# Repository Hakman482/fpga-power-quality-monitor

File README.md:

# FPGA-Based Single-Phase Power Quality Monitor

A complete hardware–FPGA–software prototype for real-time single-phase power-quality measurement, developed as an MSc Electronic & Electrical Engineering project.

The system combines a custom 4-layer sensing/conditioning PCB, dual 16-bit SAR ADC acquisition, a Nexys A7-100T FPGA processing pipeline, UART telemetry, and a Python desktop GUI. The implementation measures and visualises RMS voltage/current, frequency, active/apparent power, power factor, harmonic distortion, raw ADC samples, waveforms, and voltage-event conditions.

> **Safety:** the hardware includes circuitry intended to interface with hazardous AC voltages. The prototype is an academic/laboratory design, not a certified measurement instrument. Do not connect it to mains unless you are qualified to work on hazardous voltages and have independently verified isolation, protection, creepage/clearance, grounding, enclosure and test procedures.

## Project highlights

- Custom **4-layer PCB** for isolated voltage sensing and Hall-effect current sensing.
- Two synchronized **ADS8320 16-bit SAR ADC** channels.
- **Nexys A7-100T / Artix-7** FPGA (`xc7a100tcsg324-1`).
- **10 kS/s per channel** synchronized acquisition.
- FPGA implementations for cycle-synchronous RMS, frequency measurement, active/apparent power, power factor, adaptive harmonic analysis through the 25th harmonic, and THD calculation.
- Real-data mode selected in the supplied top-level design (`TEST_MODE => false`).
- **115200-baud UART** with separate metric and waveform/raw-ADC packet formats.
- Python/Tkinter GUI with live dashboard, waveforms, raw ADC view, spectrum, events, validation tools and CSV recording.
- Experimental validation using function-generator voltage tests and DC current calibration, with measurement-uncertainty analysis.

## System architecture

`Voltage / Current sensing -> analogue conditioning -> dual ADC -> FPGA acquisition/DSP -> UART -> Python GUI`

### Measurement hardware

The voltage path uses an isolated-amplifier-based sensing chain followed by precision op-amp conditioning and anti-alias filtering before conversion by an ADS8320.

Current is sensed using an ACS724 Hall-effect sensor, conditioned around the analogue midpoint, filtered and digitised by the second ADS8320.

## FPGA architecture

The final hardware design is in [`fpga/`](fpga/).

| Parameter | Value |
|---|---:|
| FPGA | Nexys A7-100T / `xc7a100tcsg324-1` |
| System clock | 100 MHz |
| ADC serial clock | 500 kHz |
| Sampling rate | 10 kS/s/channel |
| Nominal mains frequency | 50 Hz |
| Nominal RMS/power window | 200 samples |
| Maximum adaptive THD cycle frame | 210 samples |
| UART | 115200 baud, 8N1 |
| Waveform frame | 1000 sample pairs |
| Waveform capture interval | approximately 2 s |

See [`fpga/README.md`](fpga/README.md) for the module breakdown and Vivado build instructions.

## UART protocol and GUI

Two packet families are transmitted:

- `AA55`: FPGA-computed power-quality metrics.
- `AA56`: versioned V/I sample frames containing raw 16-bit ADC codes and scaled engineering-unit samples.

A 1000-pair frame represents 100 ms of data at 10 kS/s, or about five cycles of a 50 Hz waveform. Continuous raw streaming is deliberately avoided because 115200-baud UART cannot carry the full 10 kS/s sample stream continuously.

The Python GUI is in [`gui/`](gui/).

```bash
cd gui
python -m pip install -r requirements.txt
python main.py
```

## Validation

The project was validated using low-voltage sinusoidal input tests for the voltage chain and DC current calibration for the current chain. Oscilloscope/logic measurements were also used to verify conversion cadence, ADC serial-clock bursts and activity on both ADC data lines.

The original GUI CSV format is preserved. Most captures are stored directly as `.csv`. Four captures exceeded the transfer size used to populate this repository and are therefore stored **losslessly** as gzip-compressed CSV files:

- `validation/current/raw/raw_adc_0.05A.csv.gz`
- `validation/current/raw/raw_adc_0.2A.csv.gz`
- `validation/current/raw/raw_adc_0.25A.csv.gz`
- `validation/voltage/raw/raw_adc_cali_10pp.csv.gz`

They decompress to the original CSV bytes, e.g.:

```bash
gzip -dk validation/current/raw/raw_adc_0.25A.csv.gz
```

Known isolated acquisition glitches are preserved in the source captures. Analysis excludes isolated invalid codes such as exact `24576` and `49152` samples where they represent acquisition artefacts rather than real measurements. See [`validation/README.md`](validation/README.md).

## Hardware and manufacturing

Editable KiCad sources, the full custom footprint/symbol libraries, repository-relative 3D models, Gerbers, drill files, BOM and component-placement outputs are under [`hardware/`](hardware/).

The board source can be opened from:

```text
hardware/kicad/myProject.kicad_pro
```

## Repository layout

```text
.
├── README.md
├── .gitignore
├── CITATION.cff
├── fpga/
│   ├── src/             # final active VHDL
│   ├── sim/             # simulation/testbench sources
│   ├── legacy/          # earlier auto-disabled modules
│   ├── constraints/
│   └── scripts/
├── gui/                 # Python GUI and UART parser
├── hardware/
│   ├── kicad/
│   └── manufacturing/
├── validation/
│   ├── current/
│   ├── voltage/
│   └── analysis/
└── docs/
    ├── images/
    └── academic/
```

## Rebuilding the FPGA project

Generated Vivado cache/run files are intentionally omitted.

From Vivado Tcl:

```tcl
source fpga/scripts/create_project.tcl
```

The original project was developed with Vivado 2026.1. Re-run synthesis, implementation and timing checks in your installed Vivado release before programming hardware.

## Academic material

The project-defence presentation is included under `docs/academic/`.

The final dissertation itself is not duplicated in this Git repository; the repository is intended to expose the engineering implementation, design files, evidence and reproducible validation assets rather than act as a dissertation archive.

## Scope and limitations

This repository documents a working academic prototype rather than a certified power-quality analyser. Laboratory-source constraints limited voltage validation to low-voltage controlled inputs, and current calibration was performed at sub-ampere DC levels. Transient/event functionality was not developed into a full standards-compliant disturbance classifier.

## Author

**Hakeem Issah**  
MSc Electronic & Electrical Engineering project, 2026.

## Use and licensing

No open-source licence is asserted. The material is shared as academic/portfolio work. Contact the author before reusing substantial portions in another project or publication.

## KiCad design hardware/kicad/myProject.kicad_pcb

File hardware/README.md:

# Hardware and PCB

Editable KiCad design files and manufacturing outputs for the custom measurement PCB.

## Design source

Open:

```text
kicad/myProject.kicad_pro
```

The project includes:

- top-level schematic and hierarchical sheets,
- 4-layer PCB layout,
- custom symbols,
- custom footprints,
- 3D component models.

The board implements the voltage/current sensing and conditioning chains, ADC interfaces, reference/power circuitry and FPGA interconnect used by the prototype.

## Manufacturing outputs

`manufacturing/` contains:

- Gerber files,
- plated/non-plated drill files,
- component-placement files,
- BOM,
- JLC assembly placement/CPL export.

These are retained separately from the editable KiCad design so it is clear which files are source and which are generated fabrication outputs.

## Safety and fabrication warning

This board was built and tested as an academic prototype. Manufacturing files are provided for project traceability, not as a statement that the design is certified or suitable for direct deployment on a mains installation.

Before reproducing or energising the board, independently review at least:

- insulation/isolation ratings,
- creepage and clearance,
- fuse/protection coordination,
- earthing and oscilloscope-grounding strategy,
- component voltage/current ratings,
- PCB material and manufacturing tolerances,
- enclosure and touch protection.

Do not infer regulatory compliance from the presence of Gerbers or a successful prototype build.

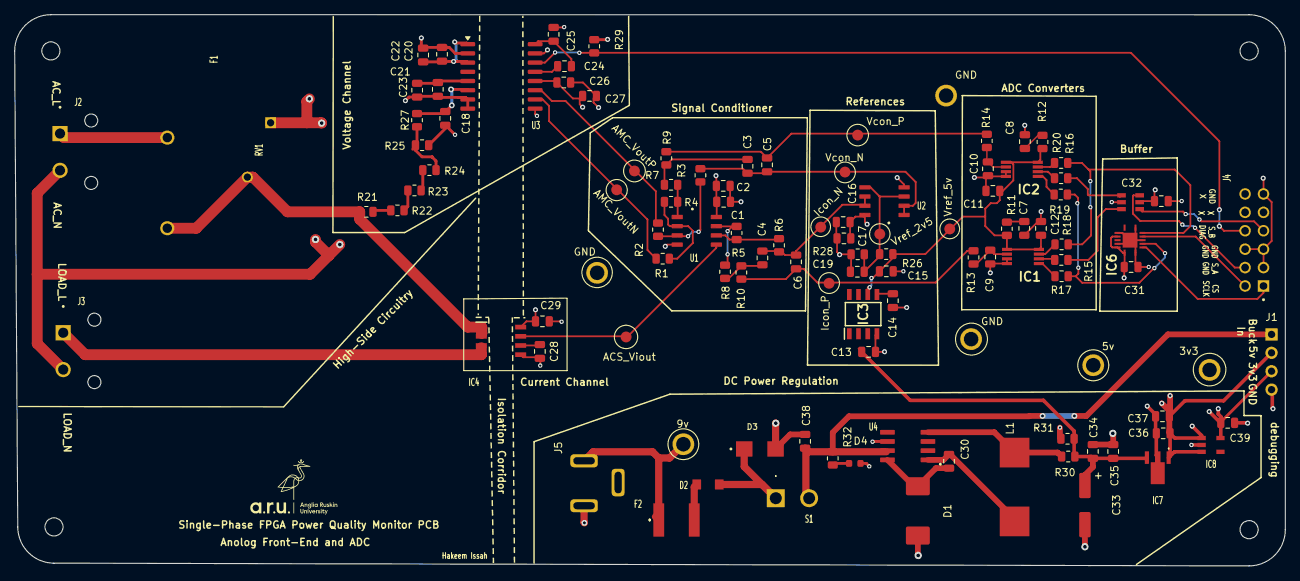
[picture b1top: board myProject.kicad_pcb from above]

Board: 4 copper layers, 175.3 x 76.1 mm, 112 parts (0 on the bottom side), 62 nets.

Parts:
3v3: +3.3V; TestPoint_Plated_Hole_D2.0mm
5v: +5V; TestPoint_Plated_Hole_D2.0mm
9v: +9V_IN; TestPoint_Plated_Hole_D2.0mm
ACS_Viout: ACS_Viout; TestPoint_Pad_D1.5mm
AMC_VoutN: AMC_VoutN; TestPoint_Pad_D1.5mm
AMC_VoutP: AMC_VoutP; TestPoint_Pad_D1.5mm
C1, C16, C21, C24, C25, C29, C31, C32, C35, C37: 100n; C_0805_2012Metric
C2, C13, C17: 4u7; C_0805_2012Metric
C3, C4, C5, C6: 33n; C_0805_2012Metric
C7, C8, C15, C39: 10u; C_0805_2012Metric
C9, C10, C18, C22, C23, C27: 1n; C_0805_2012Metric
C11, C12, C14, C19, C20, C26, C34, C36: 1u; C_0805_2012Metric
C28: 4n7; C_0805_2012Metric
C30: 10n; C_0805_2012Metric
C33: 47u; CP_Elec_6.3x5.8_custom
C38: 4.7uF; C_0805_2012Metric
D1: B340; D_SMC_custom
D2: SS34FA; SODFL3618X143Nschottky
D3: SMBJ12A; DIOM4336X265N_tvs_custom
D4: SML-D12FWT86; LED_0603_1608Metric_custom
F1: 4525holder & 0215001 fuse_catridge(installed); FUSE_4525holder
F2: SMD100F-2018-2; SMD030F20182_polyfuse
GND: GND; TestPoint_Plated_Hole_D2.0mm
GND#2, GND#3: GND; TestPoint_Plated_Hole_D2.0mm
IC1, IC2: ADS8320EB_2K5; SOP65P490X110-8N_ADC_custom
IC3: REF5050AIDR; SOIC127P600X175-8N_REF
IC4: ACS724LLCTR-05AB-T; SOIC127P600X175-8N_acs
IC5: SN74LVC2G17DBVR; SOT95P280X145-6N_buffer_a_b_custom
IC6: SN74AHCT125RGYR; RGY-_S-PVQFN-N14_cs_clk_custom
IC7: AP7375-50Y-13; AZ7042RTRG1_ldo5v
IC8: AP7375-33W5-7; SOT95P285X140-5N_ldo3.3v_custom
Icon_N: Icon_N; TestPoint_Pad_D1.5mm
Icon_P: Icon_P; TestPoint_Pad_D1.5mm
J1: Conn_01x04(debugging); PinHeader_1x04_P2.54mm_Vertical
J2: 1730395(ac_input); PHOENIX_1730395_ac_load_con
J3: 1730395(load); PHOENIX_1730395_ac_load_con
J4: 69168-112HLF; AMPHENOL_69168-112HLF_Odd_Even
J5: XDJK-0051-025_barrel; DC-470-2.1GP_C194407_barrel_custom
L1: 744770168; Inductor_new_YJYCOIN_YSPI1040T_custom
R1, R2, R3, R4, R26, R28, R30: 10k; R_0805_2012Metric
R5: 30K; R_0805_2012Metric
R6: 10K; R_0805_2012Metric
R7, R8, R9, R10, R27: 1k; R_0805_2012Metric
R11, R12: 0.22; R_0805_2012Metric
R13, R14: 100; R_0805_2012Metric
R15, R16, R17, R18, R19, R20: 47; R_0805_2012Metric
R21, R22, R23, R24: 499k; R_0805_2012Metric
R25: 4k99; R_0805_2012Metric
R29: 47k; R_0805_2012Metric
R31: 2k55; R_0805_2012Metric
R32: 2k2; R_0805_2012Metric
RV1: B72214P2271K101; B72214P2271K101MOVV
S1: L101011MS02Q; L101011MS02Q_pswitch
U1, U2: OPA2188AID; SOIC127P599X175-8Nopamp
U3: AMC3330; SOIC-16W_7.5x10.3mm_P1.27mm_custom
U4: TPS5410DR; SOIC127P599X175-8Nbuck
Vcon_N: Vcon_N; TestPoint_Pad_D1.5mm
Vcon_P: Vcon_P; TestPoint_Pad_D1.5mm
Vref_2v5: Vref_2v5; TestPoint_Pad_D1.5mm_custom
Vref_5v: Vref_5v; TestPoint_Pad_D1.5mm_custom

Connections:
+3.3V: 3v3.1, C32.1, C39.1, IC5.5 (VCC), IC8.5 (VOUT), J1.3, R29.1
+5V: 5v.1, C1.1, C2.1, C16.1, C17.1, C26.1, C27.1, C29.1, C31.1, C36.1, C37.1, IC4.8 (VCC), IC6.10 (3~OE), IC6.13 (4~OE), IC6.14 (VCC), IC7.1 (VOUT), IC8.1 (VIN), IC8.3 (EN), J1.2, U1.8 (V+), U2.8 (V+), U3.12 (VDD)
/+6V: C13.1, C33.1, C34.1, C35.1, IC7.3 (VIN), R30.2, R31.2
/+9V_IN: 9v.1, F2.1, J5.1
/ACS_Viout: ACS_Viout.1, IC4.7 (VIOUT), U1.5 (+INB)
/AC_L: F1.1, J2.1
/AC_N: C18.2, C20.2, C21.2, C22.2, C23.2, J2.2, J3.2, R25.1, RV1.1, U3.2 (DCDC_HGND), U3.7 (INN), U3.8 (HGND)
/AC_Path/FUSED_AC_L: F1.2, IC4.1 (IP+_1), IC4.2 (IP+_2), R21.1, RV1.2
/AC_Path/V_DIV: C18.1, R27.2, U3.6 (INP)
/AMC_VoutN: AMC_VoutN.1, R1.1, U3.10 (OUTN)
/AMC_VoutP: AMC_VoutP.1, R2.1, U3.11 (OUTP)
/Buck_Vin: C38.1, J1.1, R32.1, S1.2, U4.7 (VIN)
/CS: IC6.3 (1Y), R17.2, R19.2
/DIAG: J4.B4, R29.2, U3.14 (DIAG)
/DOUT_A: IC5.1 (1A), R16.2
/DOUT_B: IC5.3 (2A), R15.2
/FPGA_CS: IC6.2 (1A), J4.A1
/FPGA_SCLK: IC6.5 (2A), J4.B1
/Icon_N: C4.1, C6.1, Icon_N.1, R6.2, U2.6 (-INB), U2.7 (OUTB)
/Icon_P: C6.2, Icon_P.1, R10.2, R13.1
/LOAD_L: IC4.3 (IP-_1), IC4.4 (IP-_2), J3.1
/SCLK: IC6.6 (2Y), R18.2, R20.2
/SDO_A: IC5.6 (1Y), J4.B2
/SDO_B: IC5.4 (2Y), J4.A4
/Vcon_N: C3.2, C5.2, R3.2, U2.1 (OUTA), U2.2 (-INA), Vcon_N.1
/Vcon_P: C5.1, R9.2, R14.1, Vcon_P.1
/Vref_2v5: C19.1, R26.2, R28.1, U2.3 (+INA), U2.5 (+INB), Vref_2v5.1
/Vref_5v: C11.1, C12.1, C15.1, IC1.1 (VREF), IC1.8 (+VCC), IC2.1 (VREF), IC2.8 (+VCC), IC3.6 (VOUT), R11.1, R12.1, R26.1, Vref_5v.1
GND: C1.2, C2.2, C7.2, C8.2, C9.2, C10.2, C11.2, C12.2, C13.2, C14.2, C15.2, C16.2, C17.2, C19.2, C25.2, C26.2, C27.2, C28.2, C29.2, C31.2, C32.2, C33.2, C34.2, C35.2, C36.2, C37.2, C38.2, C39.2, D1.2 (A), D3.A, D4.2 (C), GND.1, GND#2.1, GND#3.1, IC1.3 (-IN), IC1.4 (GND), IC2.3 (-IN), IC2.4 (GND), IC3.4 (GND), IC4.5 (GND), IC5.2 (GND), IC6.1 (1~OE), IC6.4 (2~OE), IC6.7 (GND), IC6.9 (3A), IC6.12 (4A), IC6.15 (THERMAL_PAD), IC7.2 (GND_1), IC8.2 (GND), J1.4, J4.A2, J4.A3, J4.A6, J4.B3, J5.2, R28.2, R31.1, U1.4 (V-), U2.4 (V-), U3.9 (GND), U3.15 (DCDC_GND), U4.6 (GND)
unnamed: C3.1, R7.2, R9.1
unnamed: C4.2, R8.2, R10.1
unnamed: C7.1, R11.2
unnamed: C8.1, R12.2
unnamed: C30.1, D1.1 (K), U4.8 (PH)
unnamed: D2.2 (A), F2.2
unnamed: D2.1 (K), D3.C, S1.1
unnamed: D4.1 (A), R32.2
unnamed: C9.1, IC1.2 (+IN), R13.2
unnamed: IC1.7 (DCLOCK), R18.1
unnamed: IC1.6 (DOUT), R15.1
unnamed: IC1.5 (~CS/SHDN), R17.1
unnamed: C10.1, IC2.2 (+IN), R14.2
unnamed: IC2.7 (DCLOCK), R20.1
unnamed: IC2.6 (DOUT), R16.1
unnamed: IC2.5 (~CS/SHDN), R19.1
unnamed: C14.1, IC3.5 (TRIM/NR)
unnamed: C28.1, IC4.6 (FILTER)
unnamed: R21.2, R22.1
unnamed: R22.2, R23.1
unnamed: R23.2, R24.1
unnamed: R24.2, R25.2, R27.1
unnamed: R2.2, R3.1, U1.3 (+INA)
unnamed: R1.2, R4.1, U1.2 (-INA)
unnamed: R5.1, R6.1, U1.6 (-INB)
unnamed: R4.2, R7.1, U1.1 (OUTA)
unnamed: R5.2, R8.1, U1.7 (OUTB)
unnamed: C24.2, C25.1, U3.16 (DCDC_IN)
unnamed: C20.1, C22.1, U3.1 (DCDC_OUT), U3.3 (HLDO_IN)
unnamed: C21.1, C23.1, U3.5 (HLDO_OUT)
unnamed: C24.1, U3.13 (LDO_OUT)
unnamed: C30.2, L1.2, U4.1 (BOOT)
unnamed: L1.1, R30.1, U4.4 (VSENSE)

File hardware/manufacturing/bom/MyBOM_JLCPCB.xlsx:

Comment | Designator | Footprint | JLCPCB Part #（optional）
744770168 | L1 | Inductor_new_YJYCOIN_YSPI1040T_custom | C49140886
XDJK-0051-025_barrel | J5 | DC-470-2.1GP_C194407_barrel_custom | C7498153
ADS8320EB_2K5 | IC1,IC2 | SOP65P490X110-8N_ADC_custom | C22247
SN74LVC2G17DBVR | IC5 | SOT95P280X145-6N_buffer_a_b_custom | C10429
AP7375-33W5-7 | IC8 | SOT95P285X140-5N_ldo3.3v_custom | C2877825
OPA2188AID | U2,U1 | SOIC127P599X175-8Nopamp | C17271
1n | C23,C27,C22,C18,C10,C9 | C_0805_2012Metric | C701302
1730395(load) | J3 | PHOENIX_1730395_ac_load_con | C89120
10k | R1,R30,R28,R26,R4,R3,R2 | R_0805_2012Metric | C84376
TPS5410DR | U4 | SOIC127P599X175-8Nbuck | C28867
AMC3330 | U3 | SOIC-16W_7.5x10.3mm_P1.27mm_custom | C2999368
GND | TP15,GND,GND | TestPoint_Plated_Hole_D2.0mm
Vref_2v5 | Vref_2v5 | TestPoint_Pad_D1.5mm
Vref_5v | Vref_5v | TestPoint_Pad_D1.5mm
Icon_N | Icon_N | TestPoint_Pad_D1.5mm
Icon_P | Icon_P | TestPoint_Pad_D1.5mm
Vcon_N | Vcon_N | TestPoint_Pad_D1.5mm
Vcon_P | Vcon_P | TestPoint_Pad_D1.5mm
ACS_Viout | ACS_Viout | TestPoint_Pad_D1.5mm
AMC_VoutN | AMC_VoutN | TestPoint_Pad_D1.5mm
AMC_VoutP | AMC_VoutP | TestPoint_Pad_D1.5mm
+3.3V | 3v3 | TestPoint_Plated_Hole_D2.0mm
+5V | GND | TestPoint_Plated_Hole_D2.0mm
+9V_IN | 9v | TestPoint_Plated_Hole_D2.0mm
L101011MS02Q | S1 | L101011MS02Q_pswitch | C221823
B72214P2271K101 | RV1 | B72214P2271K101MOVV
2k2 | R32 | R_0805_2012Metric | C114561
2k55 | R31 | R_0805_2012Metric | C2681631
47k | R29 | R_0805_2012Metric | C126351
1k | R27,R10,R9,R8,R7 | R_0805_2012Metric | C95781
4k99 | R25 | R_0805_2012Metric | C114542
499k | R24,R23,R22,R21 | R_0805_2012Metric
47 | R20,R19,R18,R17,R16,R15 | R_0805_2012Metric | C114541
100 | R14,R13 | R_0805_2012Metric | C105577
0.22 | R12,R11 | R_0805_2012Metric | C327215
10K | R6 | R_0805_2012Metric | C84376
30K | R5 | R_0805_2012Metric | C126352
69168-112HLF | J4 | AMPHENOL_69168-112HLF_Odd_Even | C225521
1730395(ac_input) | J2 | PHOENIX_1730395_ac_load_con | C89120
Conn_01x04(debugging) | J1 | PinHeader_1x04_P2.54mm_Vertical | C492403
AP7375-50Y-13 | IC7 | AZ7042RTRG1_ldo5v | C22364247
SN74AHCT125RGYR | IC6 | RGY-_S-PVQFN-N14_cs_clk | C2675532
ACS724LLCTR-05AB-T | IC4 | SOIC127P600X175-8N_acs | C459328
REF5050AIDR | IC3 | SOIC127P600X175-8N_REF | C27804
SMD100F-2018-2 | F2 | SMD030F20182_polyfuse | C70149
4525holder & 0215001 fuse_catridge(installed) | F1 | FUSE_4525holder | C3205505
SGT520-1A T1AL250V 5x20mm Fuse | F1-FUSE | 5x20mm Fuse Cartridge (manual insert) | C41367255
SML-D12FWT86 | D4 | LED_0603_1608Metric | C22371379
SMBJ12A | D3 | DIOM4336X265N_tvs | C151251
SS34FA | D2 | SODFL3618X143Nschottky | C719833
B340 | D1 | D_SMC | C85099
10u | C39,C15,C8,C7 | C_0805_2012Metric | C126584
4.7uF | C38 | C_0805_2012Metric | C86040
100n | C37,C35,C32,C31,C29,C25,C24,C21,C16,C1 | C_0805_2012Metric | C83055
1u | C36,C34,C26,C20,C19,C14,C12,C11 | C_0805_2012Metric | C376925
47u | C33 | CP_Elec_6.3x5.8 | C970677
10n | C30 | C_0805_2012Metric | C342877
4n7 | C28 | C_0805_2012Metric | C415370
4u7 | C13,C2,C17 | C_0805_2012Metric | C86040
33n | C6,C5,C4,C3 | C_0805_2012Metric | C5375930
